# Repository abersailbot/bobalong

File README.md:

Bobalong
=======

This is the working repository of the autonomous sailing boat codenamed Bobalong

## Hardware

Bobalong has the following hardware:
    - HMC6343 Compass
    - EM408 GPS
    - Olimex Leonardo dev board

## Goals

The goals of this project is to take part in Microtransat transatlantic race (http://www.microtransat.org/) with the aim of creating a autonomous sailing boat capable of sailing across the Atlantic Ocean.

## Features

- Waypoint following
- GSM Comms(TODO)
- Sat Comms(TODO)
- Low power software design (TODO)

## BIG TODO ##

* Look at data logging
    - Provide support for different devices
* Force control system into ino file
    - code should provide support for that ino file

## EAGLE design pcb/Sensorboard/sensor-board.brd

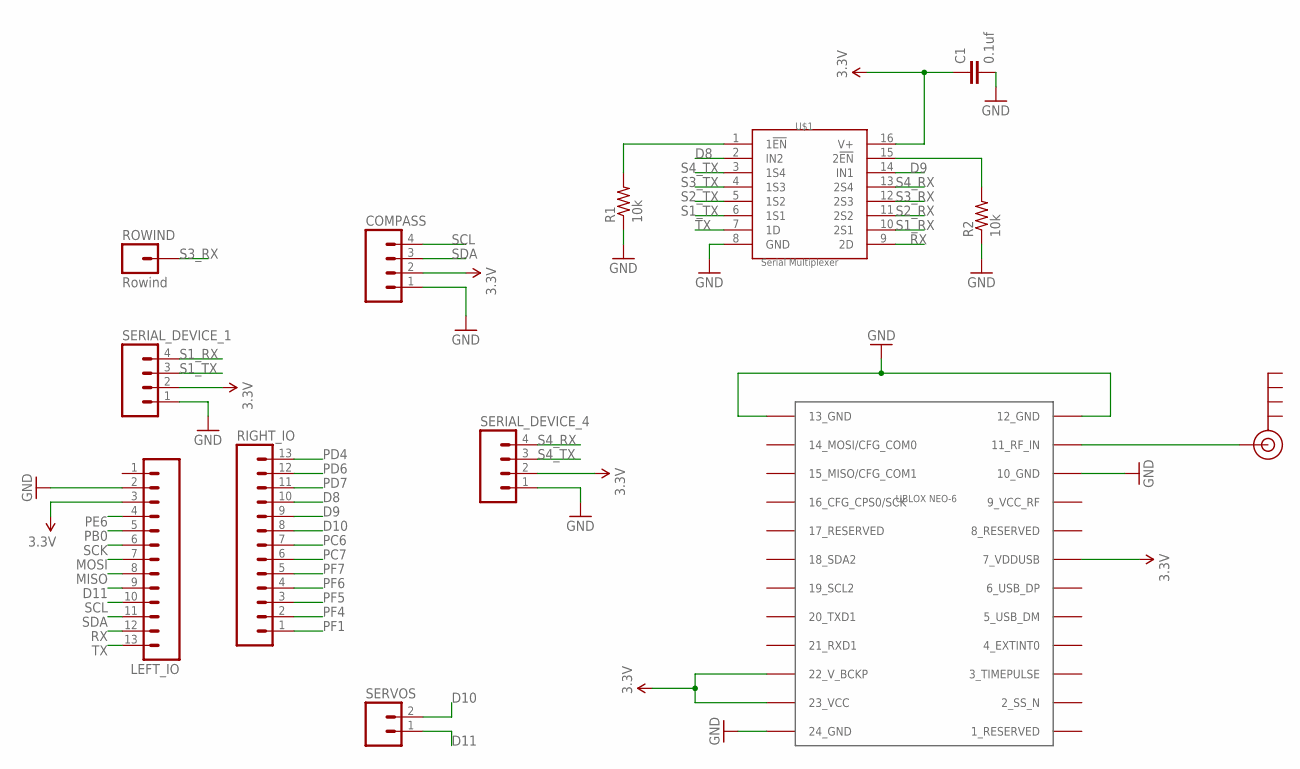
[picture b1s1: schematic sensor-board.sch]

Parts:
C1: 0.1uf; C0805
COMPASS: M04PTH; 1X04
J$1: SMA_EDGE; SMA-EDGE
LEFT_IO: M13; 1X13
R1, R2: 10k; AXIAL-0.3
RIGHT_IO: M13; 1X13
ROWIND: Rowind; 1X01
SERIAL_DEVICE_1, SERIAL_DEVICE_4: M04PTH; 1X04
SERVOS: M02PTH; 1X02
U$1: Serial Multiplexer; 16TSSOP
U$2: UBLOX_NEO-6; UBLOX_NEO-6P

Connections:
3.3V: C1.1, COMPASS.2, LEFT_IO.3, SERIAL_DEVICE_1.2, SERIAL_DEVICE_4.2, U$1.16 (V+), U$2.7_VDDUSB, U$2.22_V_BCKP, U$2.23_VCC
D8: RIGHT_IO.10, U$1.2 (IN2)
D9: RIGHT_IO.9, U$1.14 (IN1)
D10: RIGHT_IO.8, SERVOS.2
D11: LEFT_IO.9, SERVOS.1
GND: C1.2, COMPASS.1, LEFT_IO.2, R1.P$1 (1), R2.P$1 (1), SERIAL_DEVICE_1.1, SERIAL_DEVICE_4.1, U$1.8 (GND), U$2.10_GND, U$2.12_GND, U$2.13_GND, U$2.24_GND
MISO: LEFT_IO.8
MOSI: LEFT_IO.7
unnamed: R1.P$2 (2), U$1.1 (1!EN)
unnamed: R2.P$2 (2), U$1.15 (2!EN)
unnamed: J$1.SIG (SIGNAL), U$2.11_RF_IN
PB0: LEFT_IO.5
PC6: RIGHT_IO.7
PC7: RIGHT_IO.6
PD4: RIGHT_IO.13
PD6: RIGHT_IO.12
PD7: RIGHT_IO.11
PE6: LEFT_IO.4
PF1: RIGHT_IO.1
PF4: RIGHT_IO.2
PF5: RIGHT_IO.3
PF6: RIGHT_IO.4
PF7: RIGHT_IO.5
RX: LEFT_IO.12, U$1.9 (2D)
S1_RX: SERIAL_DEVICE_1.4, U$1.10 (2S1)
S1_TX: SERIAL_DEVICE_1.3, U$1.6 (1S1)
S2_RX: U$1.11 (2S2)
S2_TX: U$1.5 (1S2)
S3_RX: ROWIND.1, U$1.12 (2S3)
S3_TX: U$1.4 (1S3)
S4_RX: SERIAL_DEVICE_4.4, U$1.13 (2S4)
S4_TX: SERIAL_DEVICE_4.3, U$1.3 (1S4)
SCK: LEFT_IO.6
SCL: COMPASS.4, LEFT_IO.10
SDA: COMPASS.3, LEFT_IO.11
TX: LEFT_IO.13, U$1.7 (1D)

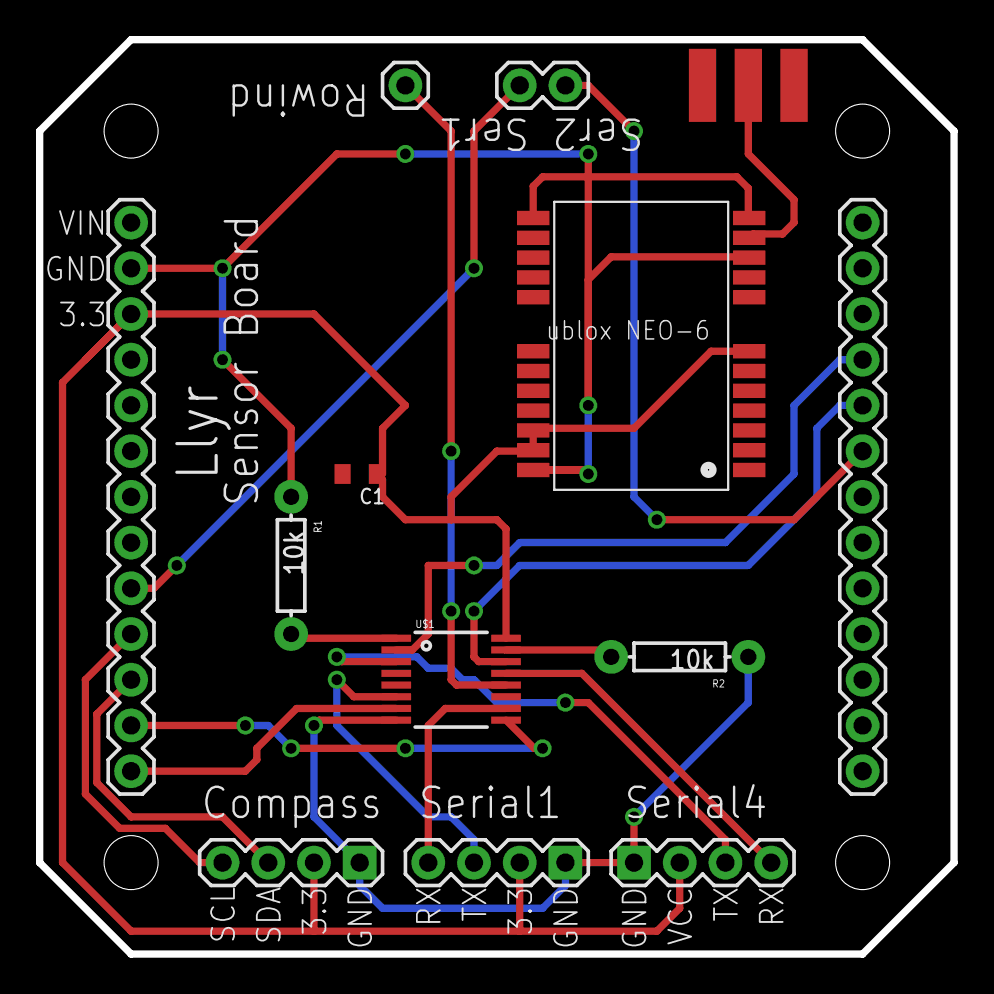
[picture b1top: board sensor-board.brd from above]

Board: 2 copper layers, 50.8 x 50.8 mm, 13 parts (0 on the bottom side), 18 nets.

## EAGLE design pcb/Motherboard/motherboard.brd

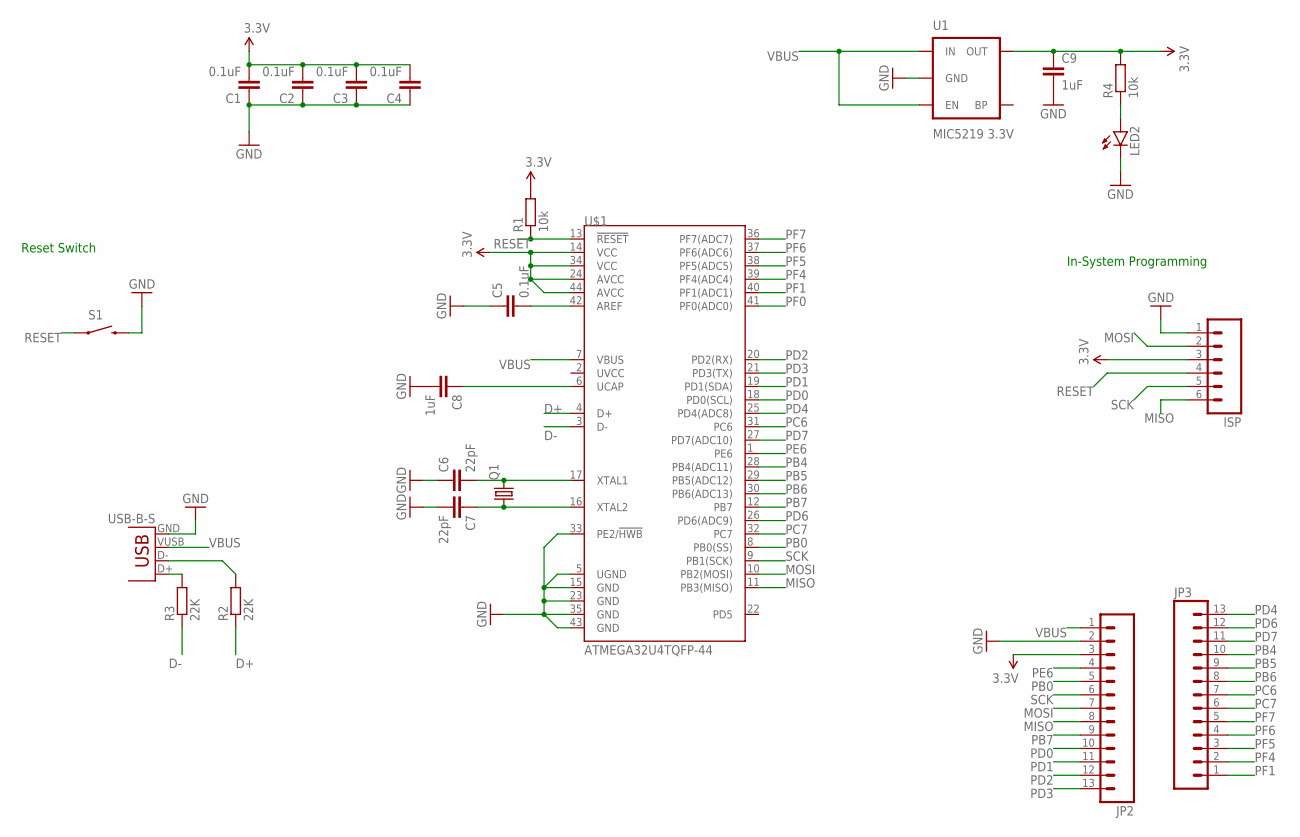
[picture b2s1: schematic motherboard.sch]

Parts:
C1, C2, C3, C4, C5: 0.1uF; C0805
C6, C7: 22pF; C0805
C8, C9: 1uF; C0805
ISP: M06SMD; 1X06-SMD
JP1: USB-B-S; USB-B-SMT
JP2, JP3: M13; 1X13
LED2: LED1206; LED-1206
Q1: CRYSTALHC49S; HC49/S
R1, R4: 10k; R0805
R2, R3: 22K; R0805
S1: SWITCH-MOMENTARY-2PTH; TACTILE-PTH
U1: MIC5219 3.3V; SOT23-5
U$1: ATMEGA32U4TQFP-44; TQFP44

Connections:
3.3V: C1.2, C2.2, C3.2, C4.2, C9.1, ISP.3, JP2.3, R1.2, R4.2, U1.5 (OUT), U$1.14 (VCC), U$1.24 (AVCC), U$1.34 (VCC), U$1.44 (AVCC)
D+: R2.1, U$1.4 (D+)
D-: R3.1, U$1.3 (D-)
GND: C1.1, C2.1, C3.1, C4.1, C5.1, C6.1, C7.2, C8.2, C9.2, ISP.1, JP1.GND, JP2.2, LED2.C, S1.3 (2), U1.2 (GND), U$1.5 (UGND), U$1.15 (GND), U$1.23 (GND), U$1.33 (PE2/!HWB), U$1.35 (GND), U$1.43 (GND)
MISO: ISP.6, JP2.8, U$1.11 (PB3(MISO))
MOSI: ISP.2, JP2.7, U$1.10 (PB2(MOSI))
unnamed: C7.1, Q1.1, U$1.16 (XTAL2)
unnamed: C5.2, U$1.42 (AREF)
unnamed: C6.2, Q1.2, U$1.17 (XTAL1)
unnamed: JP1.D+, R3.2
unnamed: JP1.D-, R2.2
unnamed: LED2.A, R4.1
unnamed: C8.1, U$1.6 (UCAP)
PB0: JP2.5, U$1.8 (PB0(SS))
PB4: JP3.10, U$1.28 (PB4(ADC11))
PB5: JP3.9, U$1.29 (PB5(ADC12))
PB6: JP3.8, U$1.30 (PB6(ADC13))
PB7: JP2.9, U$1.12 (PB7)
PC6: JP3.7, U$1.31 (PC6)
PC7: JP3.6, U$1.32 (PC7)
PD0: JP2.10, U$1.18 (PD0(SCL))
PD1: JP2.11, U$1.19 (PD1(SDA))
PD2: JP2.12, U$1.20 (PD2(RX))
PD3: JP2.13, U$1.21 (PD3(TX))
PD4: JP3.13, U$1.25 (PD4(ADC8))
PD6: JP3.12, U$1.26 (PD6(ADC9))
PD7: JP3.11, U$1.27 (PD7(ADC10))
PE6: JP2.4, U$1.1 (PE6)
PF0: U$1.41 (PF0(ADC0))
PF1: JP3.1, U$1.40 (PF1(ADC1))
PF4: JP3.2, U$1.39 (PF4(ADC4))
PF5: JP3.3, U$1.38 (PF5(ADC5))
PF6: JP3.4, U$1.37 (PF6(ADC6))
PF7: JP3.5, U$1.36 (PF7(ADC7))
RESET: ISP.4, R1.1, S1.1, U$1.13 (!RESET)
SCK: ISP.5, JP2.6, U$1.9 (PB1(SCK))
VBUS: JP1.VUSB (VBUS), JP2.1, U1.1 (IN), U1.3 (EN), U$1.7 (VBUS)

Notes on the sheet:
In-System Programming
Reset Switch

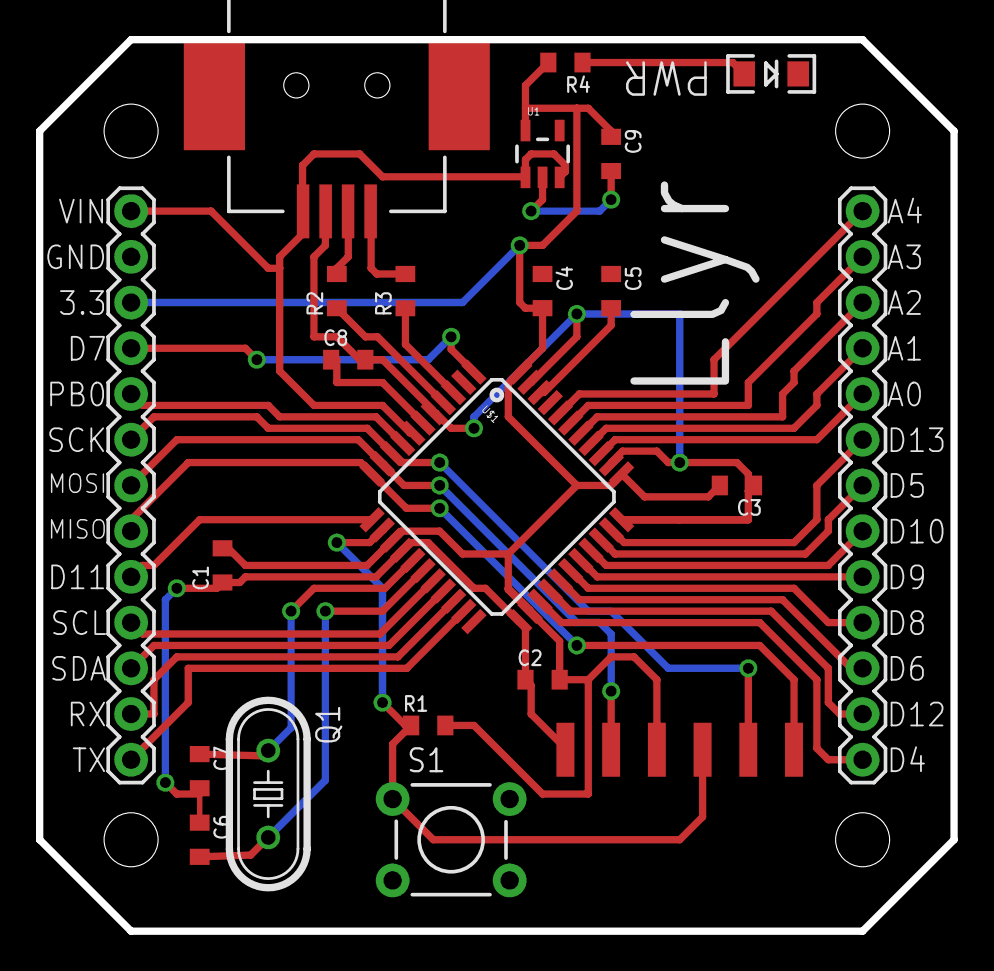
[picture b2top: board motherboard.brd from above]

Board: 2 copper layers, 50.8 x 49.5 mm, 22 parts (0 on the bottom side), 36 nets.

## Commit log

2014-10-19 -Refactored the compass into a object -Added a header file which contain definitions for utility functions
2014-10-19 -Fixed typo in compass -Refactored GPS to be an object
2014-10-19 Missed a line
2014-10-27 Updated code, refactored and moved into classes, still a work in progress
2014-10-27 Unrelated notes removed
2014-11-05 -Refactored waypoint_mgr -Started work on refactoring the high level navigation code into navigator
2014-11-13 Updated loads fo stuff, not complete
2014-11-19 Updated comments / documentation
2014-11-26 Cleared out ino and started added tests to it for hardware testing
2014-11-26 Fixed typographical errors.
2014-11-27 Fixed a ton of typos
2014-12-01 Did some more refactoring
2014-12-03 Refactored slightly
2014-12-03 Added changes done doing the code review
2014-12-06 Started on the PI controller
2014-12-06 Small bug-fix
2014-12-06 Made some values in the pid controller static so they don't reset on each call. Could do with moving the PI coeficients into config.h as defines
2014-12-07 Moved variables for the PI-controller to configure.h and navigator.h
2014-12-07 Rounding the floats before returning from GET_RUDDER_ANGLE
2014-12-09 starte testing gps, we have some odd issues with it not updating.
2014-12-10 -Tested waypoint code and GPS - Tidied up the repo more - JSpringett && David Capper
2014-12-10 Fixed the rounding in nav.cpp and moved some variables
2014-12-11 -Tested rowind -tested pid, now working correctly
2014-12-13 - implemented some simple sailing logic - PID changes, not working correctly
2015-02-11 -Began adding support for the multiplexer system - Wrote a class definition for Hardware
2015-02-17 Added a module for dealing with low level hardware - Updated the configure file to include the multiplexer
2015-02-17 Moved to ino tool
2015-02-17 Removed build files and updated gitignore to ignore future build files
2015-02-17 Updated the rowind to use the new multiplexer system instead of software serial
2015-02-22 Added pcb
2015-02-24 - Updated PCB to include bigger components, 805 instead of 804 - Improved PCB layout
2015-02-26 Added GSM.cpp and GSM.h
2015-03-05 Added sensor board and reorganized
2015-03-06 Began massive code refactor
2015-03-10 Cleaned up ino file
2015-03-13 Code wouldn't upload because I had not set the upload board model
2015-03-17 Made a couple changes and fixed some stuff
2015-03-17 Prepared the code for a autonomous carpark test
2015-03-18 Fixed a bunch of bugs and created better logging code
2015-03-18 Applied a fix to getting the time from the GPS, needs testing
2015-03-22 Made some changes to the waypoint code
2015-03-23 Fixed some compass issues
2015-03-24 Removed temp rudder setting function
2015-03-24 Completed implementation of the SDLogger class which clears up logging to the SD card we use
2015-03-25 Implemented a boat state struct and added pid data logging
2015-04-03 number of changes and little fixes after a car park and sail
2016-01-20 Add stub docs
2016-01-20 Change docs theme

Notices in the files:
parts and their libraries:
SparkFun-Connectors: Licensing: Creative Commons ShareAlike 4.0 International - https://creativecommons.org/licenses/by-sa/4.0
ELL-i-Passives: Originally copied from SparkFun-Passives.lbr, under SparkFun Creative Commons license.
